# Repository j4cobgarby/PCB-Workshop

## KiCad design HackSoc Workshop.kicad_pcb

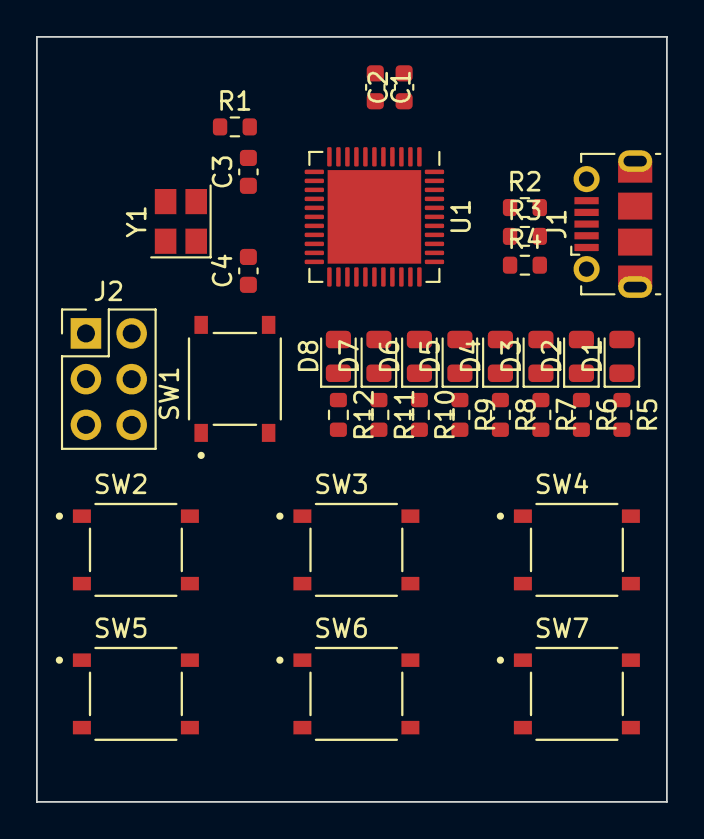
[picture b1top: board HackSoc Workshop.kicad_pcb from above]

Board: 2 copper layers, 35.0 x 42.5 mm, 35 parts (0 on the bottom side), 30 nets, no tracks yet.

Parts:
C1: 1u; C_0603_1608Metric
C2: 10u; C_0603_1608Metric
C3, C4: 22pF; C_0603_1608Metric
D1, D2, D3, D4, D5, D6, D7, D8: LED; LED_0805_2012Metric
J1: USB_B_Micro; USB_Micro-B_Molex-105017-0001
J2: ISP; PinHeader_2x03_P2.54mm_Vertical
R1, R4: 10k; R_0603_1608Metric
R2, R3: 22; R_0603_1608Metric
R5, R6, R7, R8, R9, R10, R11, R12: 270; R_0603_1608Metric
SW1, SW2, SW3, SW4, SW5, SW6, SW7: SW_Push; SW_TS-1187A-B-A-B
U1: ATmega32U4-M; QFN-44-1EP_7x7mm_P0.5mm_EP5.2x5.2mm
Y1: 12MHz; Crystal_SMD_3225-4Pin_3.2x2.5mm

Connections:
GND: C1.1, C2.2, C3.2, C4.2, J1.5 (GND), J1.6 (Shield), J2.6, R4.2, R5.2, R6.2, R7.2, R8.2, R9.2, R10.2, R11.2, R12.2, U1.5 (UGND), U1.15 (GND), U1.23 (GND), U1.35 (GND), U1.43 (GND), U1.45 (GND)
unnamed: C1.2, U1.6 (UCAP)
unnamed: D1.1 (K), R5.1
unnamed: D1.2 (A), U1.18 (PD0)
unnamed: D2.1 (K), R6.1
unnamed: D2.2 (A), U1.19 (PD1)
unnamed: D3.1 (K), R7.1
unnamed: D3.2 (A), U1.20 (PD2)
unnamed: D4.1 (K), R8.1
unnamed: D4.2 (A), U1.21 (PD3)
unnamed: D5.1 (K), R9.1
unnamed: D5.2 (A), U1.25 (PD4)
unnamed: D6.1 (K), R10.1
unnamed: D6.2 (A), U1.22 (PD5)
unnamed: D7.1 (K), R11.1
unnamed: D7.2 (A), U1.26 (PD6)
unnamed: D8.1 (K), R12.1
unnamed: D8.2 (A), U1.27 (PD7)
unnamed: J1.2 (D-), R3.2
unnamed: J1.3 (D+), R2.2
unnamed: J2.1, U1.11 (PB3)
unnamed: J2.3, U1.9 (PB1)
unnamed: J2.4, U1.10 (PB2)
unnamed: J2.5, R1.2, U1.13 (~RESET)
unnamed: R2.1, U1.4 (D+)
unnamed: R3.1, U1.3 (D-)
unnamed: R4.1, U1.33 (~HWB/PE2)
VCC: C2.1, J1.1 (VBUS), J2.2, R1.1, U1.2 (UVCC), U1.7 (VBUS), U1.14 (VCC), U1.24 (AVCC), U1.34 (VCC), U1.44 (AVCC)
XTAL1: C4.1, U1.17 (XTAL1), Y1.1
XTAL2: C3.1, U1.16 (XTAL2), Y1.2

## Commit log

2023-02-28 stuff
2023-02-28 remove PCB layout
2023-02-28 remove pcb
